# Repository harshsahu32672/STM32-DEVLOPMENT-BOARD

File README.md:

#  STM32L433CBT6 Custom Development Board  

A fully custom-designed **STM32L433CBT6 development board** built using **KiCad**, featuring USB connectivity, debugging support, and optimized PCB layout for embedded applications.

---

## 📌 Overview  
This project focuses on designing a compact and efficient development board based on the **STM32L4 series (ARM Cortex-M4)**. It includes all essential peripherals required for development, debugging, and prototyping.

---

## 🔧 Features  

- ⚡ **MCU:** STM32L433CBT6 (Ultra-low-power Cortex-M4)  
- 🔌 **Power Supply:** 5V input with onboard 3.3V regulation  
- 💻 **USB Support:** USB interface with ESD protection  
- 🔄 **USB-to-UART:** CP2102N for serial communication  
- 🧰 **Debugging:** SWD (SWCLK, SWDIO, NRST)  
- ⏱️ **Clock:**  
  - 8 MHz external crystal  
  - 32.768 kHz RTC crystal  
- 🔘 **Controls:** Reset & Boot buttons  
- 💡 **Indicators:** Power LED & User LED  
- 📡 **GPIO Access:** All major pins broken out for easy use  
- 📐 **Design:** Clean routing, proper grounding, and compact layout  

---

## 🖼️ Preview  

### 3D View  

### Schematic  

---

## 🛠️ Tools Used  

- **KiCad** – Schematic & PCB Design  
- **STM32CubeIDE / STM32CubeMX** – Firmware development  

---

## 📂 Project Structure  

STM32_Dev_Board/
│── Hardware/
│ ├── Schematic/
│ ├── PCB/
│ ├── Gerber/
│── docs/
│ ├── pcb_layout.png
│ ├── 3d_view.png
│ ├── schematic.png
│── README.md

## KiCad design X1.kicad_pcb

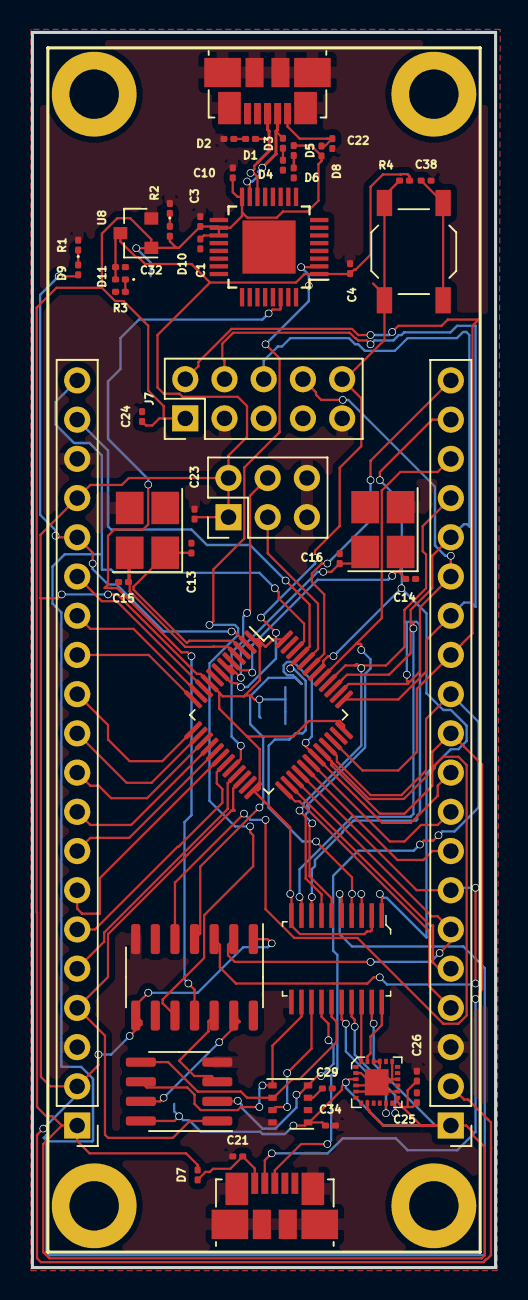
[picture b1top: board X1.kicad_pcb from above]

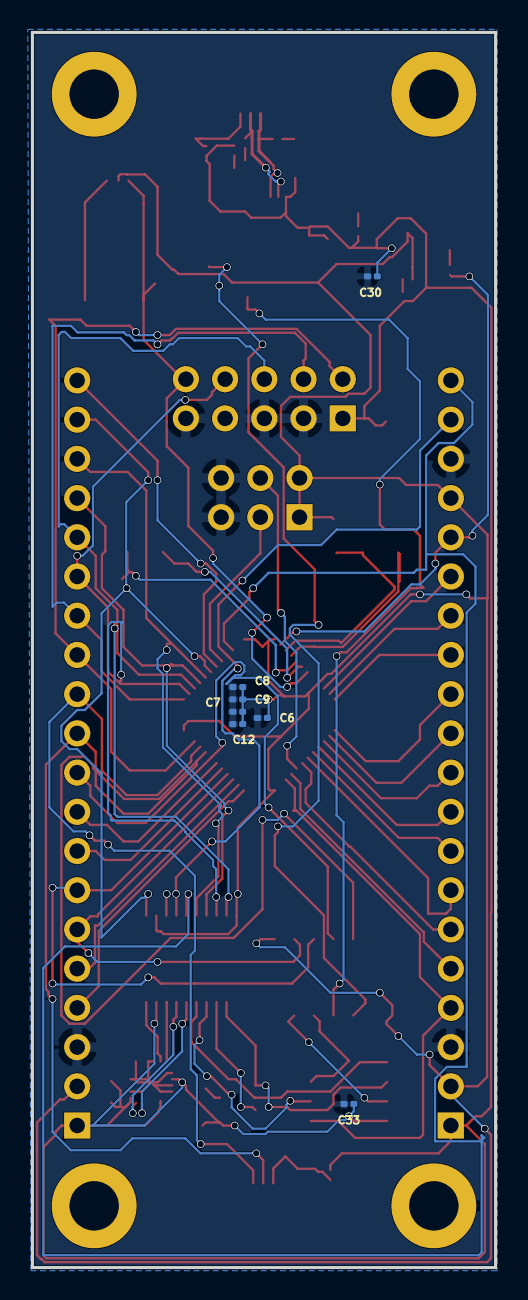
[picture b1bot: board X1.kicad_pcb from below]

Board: 2 copper layers, 30.0 x 80.0 mm, 61 parts (7 on the bottom side), 65 nets.

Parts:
C1, C3, C4, C10, C13, C14, C15, C16, C24, C30, C32, C38: C_Small; C_0201_0603Metric
C6, C7, C8, C9, C12, C21, C22: 10N; C_0201_0603Metric
C23, C25, C26, C29, C33, C34: 0.1U; C_0201_0603Metric
D1, D2, D3, D4, D5, D6: 1.5KExxA; R_0201_0603Metric
D7, D8: DIODE; R_0201_0603Metric
D9, D10, D11: LED; LED_0201_0603Metric
J1, J2, J3, J4: Conn_01x01; MountingHole_3.2mm_M3_ISO14580_Pad
J5, J6: USB_B_Micro; USB_Micro-B_Molex_47346-0001
J7: Conn_ARM_JTAG_SWD_10; PinHeader_2x05_P2.54mm_Vertical
J8: Conn_02x03_Counter_Clockwise; PinHeader_2x03_P2.54mm_Vertical
J9, J10: Conn_01x20; PinHeader_1x20_P2.54mm_Vertical
R1, R2, R3, R4: R; R_0201_0603Metric
S1: GPTS203211B; SW_SPST_TL3342
U1: STM32F103C8Tx; LQFP-48_7x7mm_P0.5mm
U2: CY7C65213A-32LTXI; LQFP-32-1EP_5x5mm_P0.5mm_EP3.45x3.45mm
U3: TXB0104D; SOIC-14_3.9x8.7mm_P1.27mm
U4: TXB0108PWR; TSSOP-20_W4.4mm
U5: W25Q64FV; SOIC-8_3.9x4.9mm_P1.27mm
U6: MPU-9150; QFN-24-1EP_3x3mm
U7: BME680; Bosch_LGA-8_3x3mm_P0.8mm_ClockwisePinNumbering
U8: LF33_TO220; SOT-23
Y1, Y2: Crystal_GND23_Small; Crystal_SMD_3225-4Pin_3.2x2.5mm_HandSoldering

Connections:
+3V3: C4.1, C6.1, C7.1, C8.1, C9.1, C12.1, C23.1, C29.1, C32.1, D11.2, J8.1, J8.2, J9.2, J9.17, J10.2, R4.1, U1.1, U1.9, U1.24, U1.36, U1.48, U2.1, U3.1, U3.8, U4.2, U4.10, U7.6, U8.3
+5V: C1.1, C3.1, C10.1, C24.1, C25.1, C26.1, C30.1, C33.1, C34.1, D5.1, D7.2, D8.2, D10.2, J7.1, J9.1, J10.1, U2.16, U2.18, U2.19, U3.14, U4.19, U5.8, U6.3, U6.8, U6.13, U7.8, U8.1
/BOOT0: J8.3, U1.44
/CLK: U4.12, U5.6, U7.4
/CS: U4.13, U7.2
/D+: D1.1, J6.3, U2.14
/D-: D3.1, J6.2, U2.15
/FSYNC: U4.16, U6.11
/HOLD: U3.13, U5.7
/INT: U4.17, U6.12
/LED: D9.2, J9.16, U1.2
/MISO: U4.14, U5.2, U7.5
/MOSI: U4.15, U5.5, U7.3
/NRST: J7.10, R4.2, S1.1, U1.7
/OSC_8_IN: C14.1, U1.5, Y2.1
/OSC_8_OUT: C16.1, U1.6, Y2.4
/OSC_32_IN: C13.1, U1.3, Y1.1
/OSC_32_OUT: C15.1, U1.4, Y1.4
/PA0: J9.15, U1.10
/PA1: J9.14, U1.11
/PA2: J9.13, U1.12
/PA3: J9.12, U1.13
/PA4: J9.11, U1.14
/PA5: J9.10, U1.15
/PA6: J9.9, U1.16
/PA7: J9.8, U1.17
/PA8: J10.8, U1.29
/PA9: J10.9, U1.30
/PA10: J10.10, U1.31, U3.4
/PA11: J5.2, J10.11, U1.32, U3.5
/PA12: J5.3, J10.12, U1.33
/PA13: J7.2, J10.13, U1.34
/PA14: J7.4, J10.14, U1.37
/PA15: J7.8, J10.15, U1.38, U4.8
/PB0: J9.7, U1.18
/PB1: J9.6, U1.19
/PB2: J8.4, U1.20
/PB3: J7.6, J10.16, U1.39, U4.9
/PB4: J10.17, U1.40, U4.7
/PB5: J10.18, U1.41, U4.6
/PB6: J10.19, U1.42, U4.1
/PB7: J10.20, U1.43, U4.3
/PB8: J9.19, U1.45, U4.4
/PB9: J9.20, U1.46, U4.5
/PB10: J9.5, U1.21
/PB11: J9.4, U1.22, U5.1
/PB12: J10.4, U1.25
/PB13: J10.5, U1.26
/PB14: J10.6, U1.27, U3.2
/PB15: J10.7, U1.28, U3.3
/RX: U2.2, U3.10
/SCLK: U4.20, U6.23
/SDA: U4.18, U6.24
/TX: U2.30, U3.11
/WR_PR: U3.12, U5.3
GND: C1.2, C3.2, C4.2, C6.2, C7.2, C8.2, C9.2, C10.2, C12.2, C13.2, C14.2, C15.2, C16.2, C21.1, C22.1, C23.2, C24.2, C25.2, C26.2, C29.2, C30.2, C32.2, C33.2, C34.2, C38.2, D2.1, D4.1, D6.1, J5.5, J5.6, J6.5, J6.6, J7.3, J7.5, J7.9, J8.5, J8.6, J9.3, J9.18, J10.3, R1.2, R2.2, R3.2, U1.8, U1.23, U1.35, U1.47, U2.4, U2.17, U2.20, U2.24, U3.7, U4.11, U5.4, U6.9, U6.15, U6.17, U6.18, U7.1, U7.7, U8.2, Y1.2, Y1.3, Y2.2, Y2.3
unnamed: C21.2, D7.1, J5.1
unnamed: C22.2, D8.1, J6.1
unnamed: C38.1, S1.2
unnamed: D1.2, D2.2
unnamed: D3.2, D4.2
unnamed: D5.2, D6.2
unnamed: D9.1, R1.1
unnamed: D10.1, R2.1
unnamed: D11.1, R3.1

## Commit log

2026-04-18 test
2026-04-18 Initial PCB project commit
